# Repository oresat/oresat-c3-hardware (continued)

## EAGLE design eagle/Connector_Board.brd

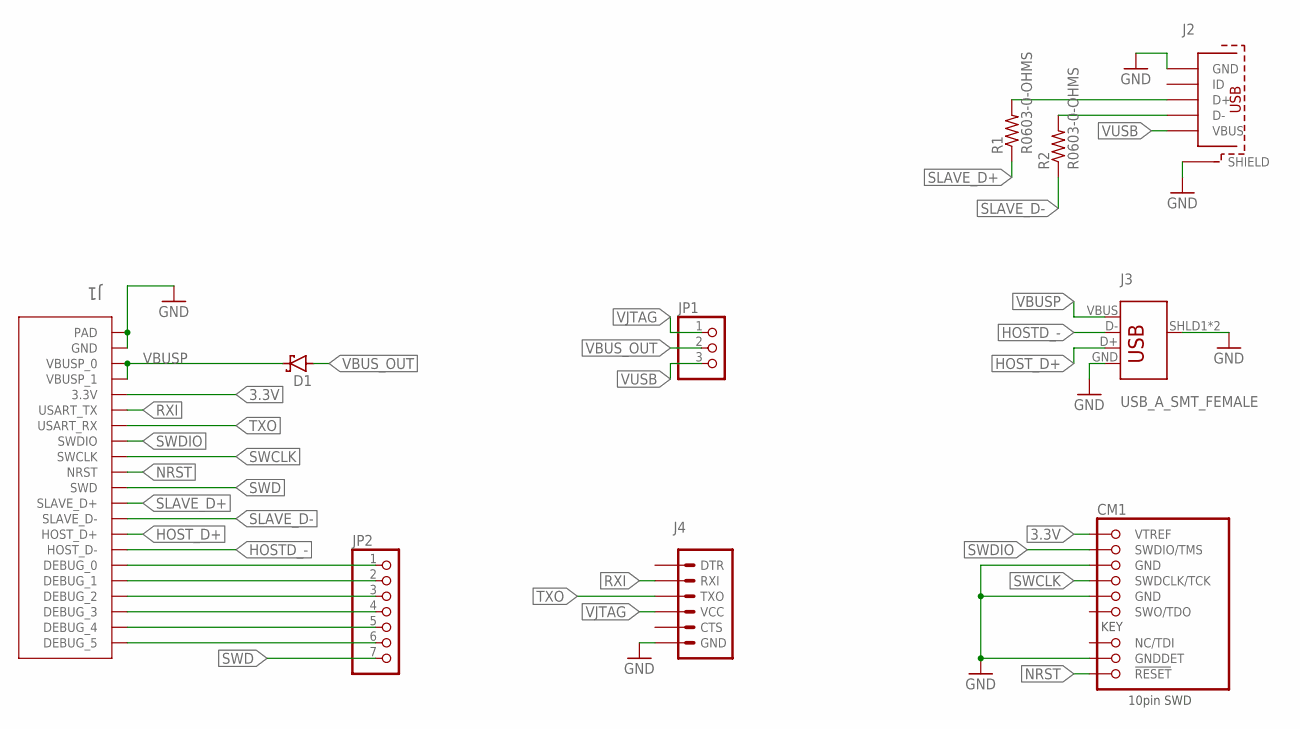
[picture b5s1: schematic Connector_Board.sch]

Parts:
CM1: FTSH-105-XX-X-DV-K; CON10_2X5_DUK_FTSH
D1: CDBU0520; DIOC1709X85N
J1: 2-1734592-0; TE_2-1734592-0
J2: MICRO-USB-SOCKET; 629105136821
J3: USB_A_SMT_FEMALE; USB-A-S-SILK-FEMALE
J4: 6_PIN_SERIAL_TARGETSILK; 6_PIN_SERIAL_TARGET_SIDE_W_SILK
JP1: PINHD-1X3; 1X03
JP2: PINHD-1X7; 1X07
R1, R2: R0603-0-OHMS; .0603-C-NOSILK

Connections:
3.3V: CM1.1 (VTREF), J1.17 (3.3V)
GND: CM1.3 (GND), CM1.5 (GND), CM1.9 (GNDDET), J1.20 (GND), J1.S1 (PAD), J1.S2 (PAD), J2.5 (GND), J2.SHELL (SHIELD), J2.SHELL1 (SHIELD), J2.SHELL2 (SHIELD), J2.SHELL3 (SHIELD), J3.GND, J3.SHLD1 (SHIELD), J3.SHLD2 (SHIELD), J4.P$6 (GND)
HOSTD_-: J1.7 (HOST_D-), J3.D-
HOST_D+: J1.8 (HOST_D+), J3.D+
unnamed: J1.6 (DEBUG_0), JP2.1
unnamed: J1.5 (DEBUG_1), JP2.2
unnamed: J1.4 (DEBUG_2), JP2.3
unnamed: J2.2 (D-), R2.2
unnamed: J2.3 (D+), R1.2
unnamed: J1.3 (DEBUG_3), JP2.4
unnamed: J1.2 (DEBUG_4), JP2.5
unnamed: J1.1 (DEBUG_5), JP2.6
NRST: CM1.10 (!RESET), J1.12 (NRST)
RXI: J1.16 (USART_TX), J4.P$3 (RXI)
SLAVE_D+: J1.10 (SLAVE_D+), R1.1
SLAVE_D-: J1.9 (SLAVE_D-), R2.1
SWCLK: CM1.4 (SWDCLK/TCK), J1.13 (SWCLK)
SWD: J1.11 (SWD), JP2.7
SWDIO: CM1.2 (SWDIO/TMS), J1.14 (SWDIO)
TXO: J1.15 (USART_RX), J4.P$2 (TXO)
VBUSP: D1.1 (C), J1.18 (VBUSP_1), J1.19 (VBUSP_0), J3.VBUS
VBUS_OUT: D1.2 (A), JP1.2
VJTAG: J4.P$4 (VCC), JP1.1
VUSB: J2.1 (VBUS), JP1.3

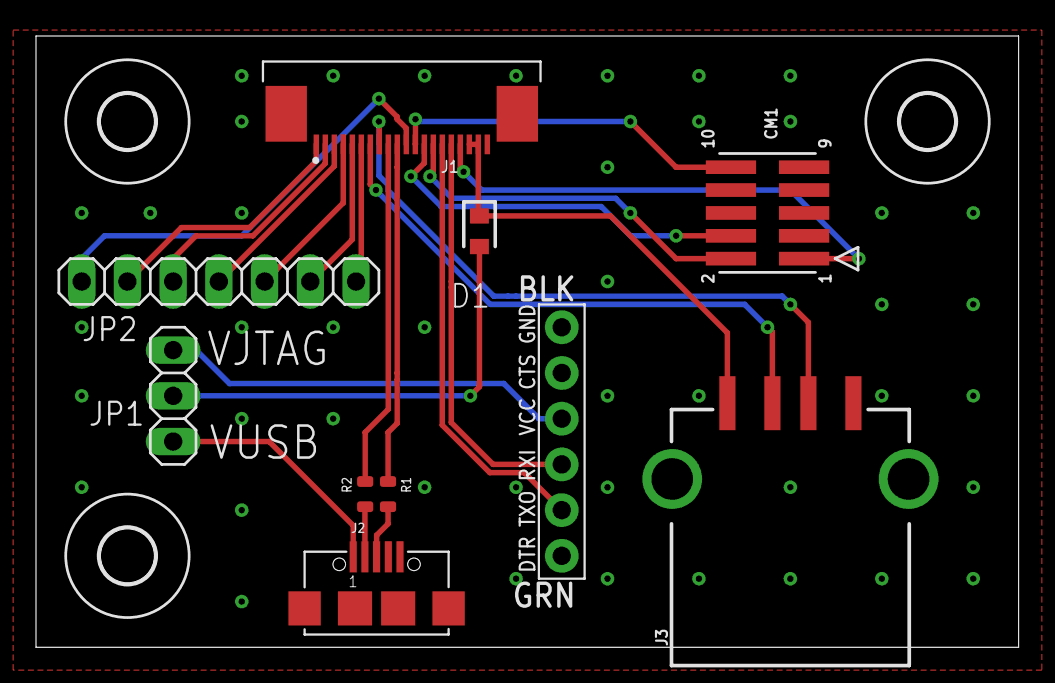
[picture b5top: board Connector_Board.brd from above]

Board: 2 copper layers, 54.6 x 34.0 mm, 13 parts (0 on the bottom side), 24 nets.

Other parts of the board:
U$1, U$2, U$3: 3,0

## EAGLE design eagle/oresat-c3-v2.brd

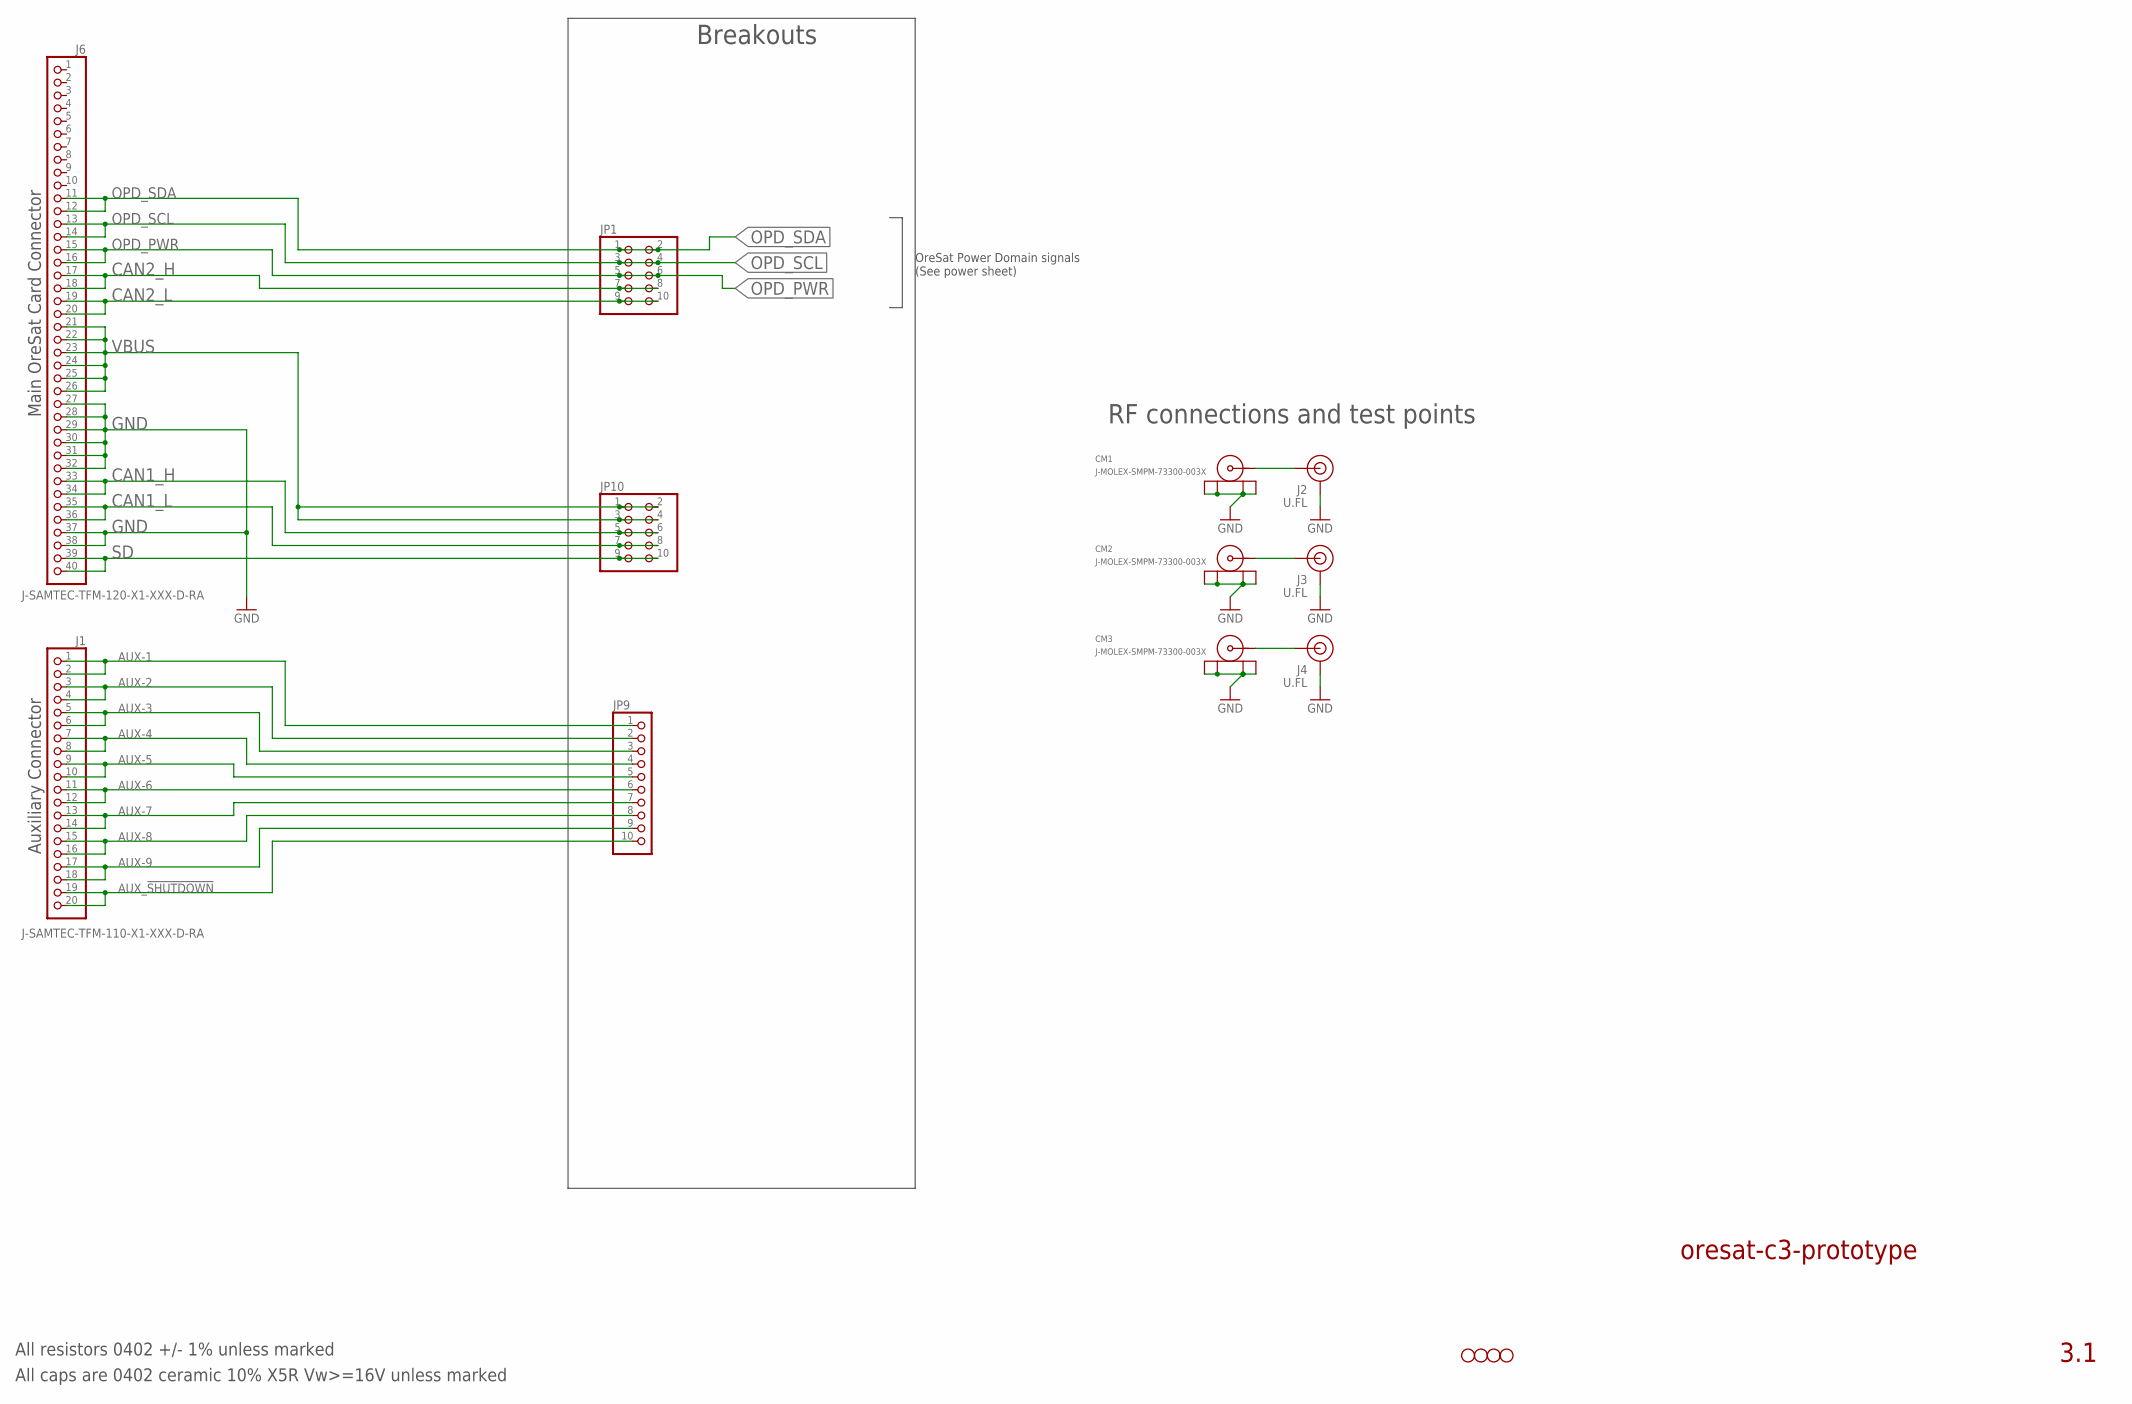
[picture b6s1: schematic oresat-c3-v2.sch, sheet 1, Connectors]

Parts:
CM1, CM2, CM3: J-MOLEX-SMPM-73300-003X; J-MOLEX-SMPM-073300-003X; MPN 73300-0020
H1, H2, H3, H4: STAND-OFFTIGHT; STAND-OFF-TIGHT
J1: J-SAMTEC-TFM-110-X1-XXX-D-RA; MPN TFM-110-01-L-D-RA
J2, J3, J4: U.FL
J6: J-SAMTEC-TFM-120-X1-XXX-D-RA; MPN TFM-120-01-L-D-RA
JP1, JP10: PINHD-2X5; 2X05
JP9: PINHD-1X10; 1X10

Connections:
AUX-1: J1.1, J1.2, JP9.1
AUX-2: J1.3, J1.4, JP9.2
AUX-3: J1.5, J1.6, JP9.3
AUX-4: J1.7, J1.8, JP9.4
AUX-5: J1.9, J1.10, JP9.5
AUX-6: J1.11, J1.12, JP9.6
AUX-7: J1.13, J1.14, JP9.7
AUX-8: J1.15, J1.16, JP9.8
AUX-9: J1.17, J1.18, JP9.9
AUX_!SHUTDOWN: J1.19, J1.20, JP9.10
CAN1_H: J6.33, J6.34, JP10.5, JP10.6; also elsewhere on the board
CAN1_L: J6.35, J6.36, JP10.7, JP10.8; also elsewhere on the board
CAN2_H: J6.17, J6.18, JP1.7, JP1.8; also elsewhere on the board
CAN2_L: J6.19, J6.20, JP1.9, JP1.10; also elsewhere on the board
GND: CM1.P$1 (SHIELD3), CM1.P$2 (SHIELD2), CM1.P$3 (SHIELD1), CM1.P$4 (SHIELD), CM2.P$1 (SHIELD3), CM2.P$2 (SHIELD2), CM2.P$3 (SHIELD1), CM2.P$4 (SHIELD), CM3.P$1 (SHIELD3), CM3.P$2 (SHIELD2), CM3.P$3 (SHIELD1), CM3.P$4 (SHIELD), J2.1 (GND), J2.2 (GND), J3.1 (GND), J3.2 (GND), J4.1 (GND), J4.2 (GND), J6.27, J6.28, J6.29, J6.30, J6.31, J6.32, J6.37, J6.38; also elsewhere on the board
unnamed: CM3.RF (CENTER), J4.FEED (SIGNAL)
OPD_PWR: J6.15, J6.16, JP1.5, JP1.6; also elsewhere on the board
OPD_SCL: J6.13, J6.14, JP1.3, JP1.4; also elsewhere on the board
OPD_SDA: J6.11, J6.12, JP1.1, JP1.2; also elsewhere on the board
RF1: CM1.RF (CENTER), J2.FEED (SIGNAL)
RF2: CM2.RF (CENTER), J3.FEED (SIGNAL)
SD: J6.39, J6.40, JP10.9, JP10.10; also elsewhere on the board
VBUS: J6.21, J6.22, J6.23, J6.24, J6.25, J6.26, JP10.1, JP10.2, JP10.3, JP10.4; also elsewhere on the board

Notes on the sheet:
oresat-c3-prototype
3.1
All resistors 0402 +/- 1% unless marked
All caps are 0402 ceramic 10% X5R Vw>=16V unless marked
Auxiliary Connector
Main OreSat Card Connector
RF connections and test points
Breakouts
OreSat Power Domain signals (See power sheet)

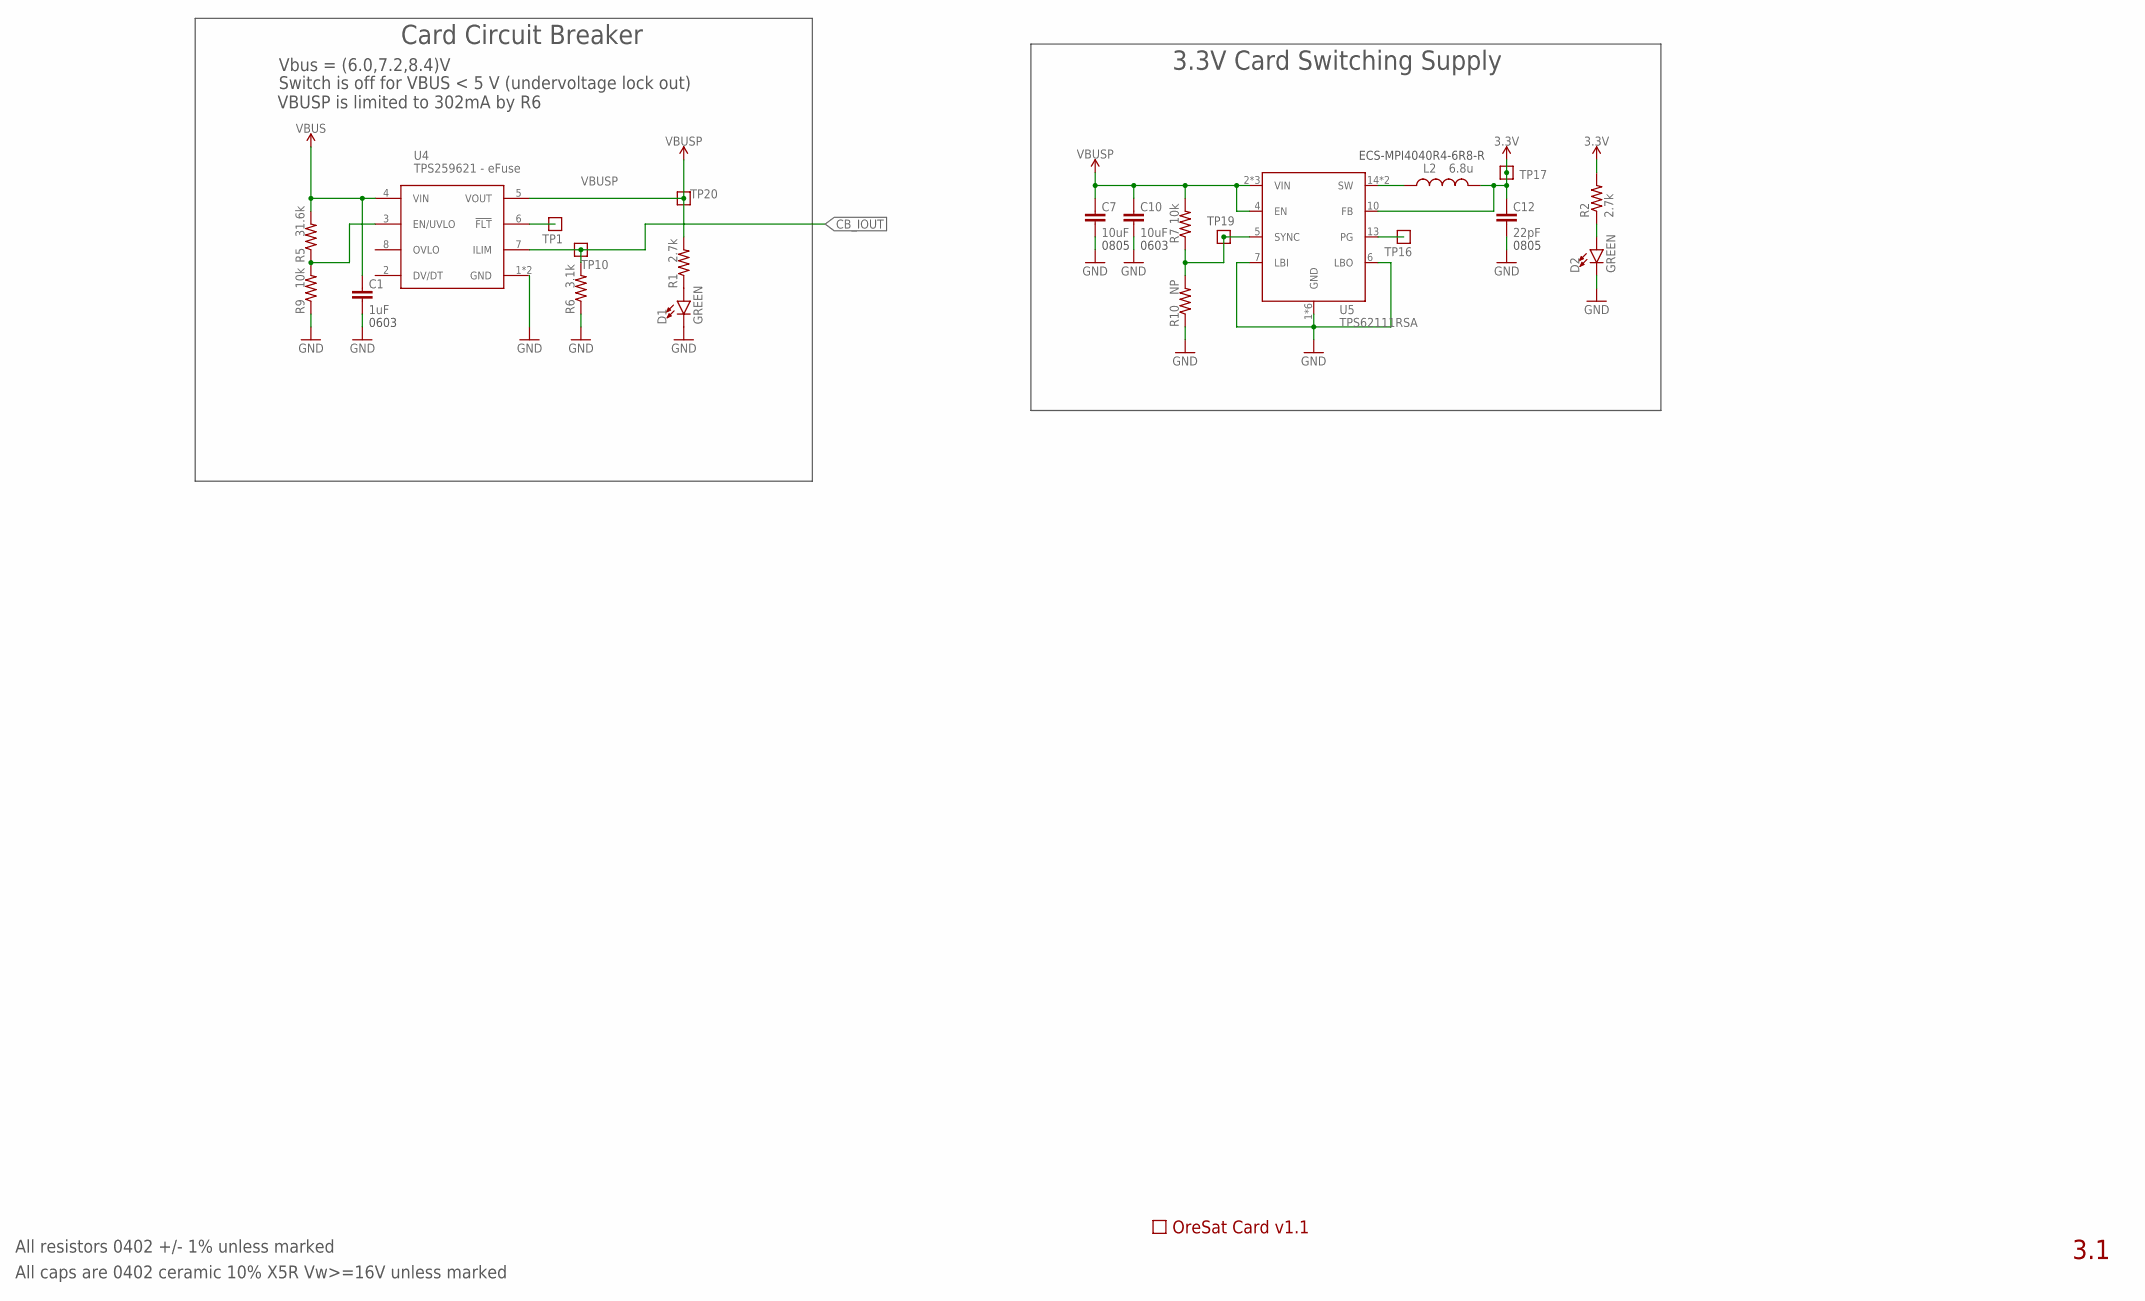
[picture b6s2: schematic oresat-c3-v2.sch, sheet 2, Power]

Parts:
C1: 1uF; .0603-B-NOSILK; MPN CL05B104KO5NNNC
C7: 10uF; .0603-B-NOSILK
C10: 10uF; .0603-B-NOSILK; MPN CL05B104KO5NNNC
C12: 22pF; .0603-B-NOSILK
D1, D2: GREEN; LED-0603
L2: 6.8u; ECS-MPI4040; MPN ECS-MPI4040R4-6R8-R
R1, R2: 2.7k; .0603-C-NOSILK; MPN RC1005F6653CS
R5: 31.6k; .0603-C-NOSILK; MPN RC1005F6653CS
R6: 3.1k; .0603-C-NOSILK; MPN RC1005F6653CS
R7, R9: 10k; .0603-C-NOSILK; MPN RC1005F6653CS
R10: NP; .0603-C-NOSILK; MPN RC1005F6653CS
TP1, TP10, TP16, TP17, TP19, TP20: TEST-POINT; 2MM-TEST-POINT
U4: TPS259621 - eFuse; SO-POWERPAD-8
U5: TPS62111RSA; S-PVQFN-16; MPN TPS62111RSA
U$1: ORESAT-CARD-V1.1-3XRF

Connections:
3.3V: C12.1, L2.2, R2.2, TP17.1, U5.10 (FB); also elsewhere on the board
!CB_FLT: TP1.1, U4.6 (!FLT)
CB_IOUT: R6.2, TP10.1, U4.7 (ILIM); also elsewhere on the board
EN/UVLO: R5.1, R9.2, U4.3 (EN/UVLO)
GND: C1.2, C7.2, C10.2, C12.2, D1.C, D2.C, R6.1, R9.1, R10.1, U4.1 (GND), U4.THERMAL (GND), U5.1 (GND), U5.6 (LBO), U5.7 (LBI), U5.9 (GND), U5.11 (GND), U5.12 (GND), U5.16 (GND), U5.PAD (GND); also elsewhere on the board
unnamed: D1.A, R1.1
unnamed: D2.A, R2.1
TPS62111-PG: TP16.1, U5.13 (PG)
TPS62111-SYNC: R7.1, R10.2, TP19.1, U5.5 (SYNC)
TPS62111_SW: L2.1, U5.14 (SW), U5.15 (SW)
VBUS: C1.1, R5.2, U4.4 (VIN); also elsewhere on the board
VBUSP: C7.1, C10.1, R1.2, R7.2, TP20.1, U4.5 (VOUT), U5.2 (VIN), U5.3 (VIN), U5.4 (EN), U5.8 (VIN); also elsewhere on the board

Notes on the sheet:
0805
0603
ECS-MPI4040R4-6R8-R
3.3V Card Switching Supply
3.1
Vbus = (6.0,7.2,8.4)V
Card Circuit Breaker
Switch is off for VBUS < 5 V (undervoltage lock out)
VBUSP is limited to 302mA by R6
All resistors 0402 +/- 1% unless marked
All caps are 0402 ceramic 10% X5R Vw>=16V unless marked

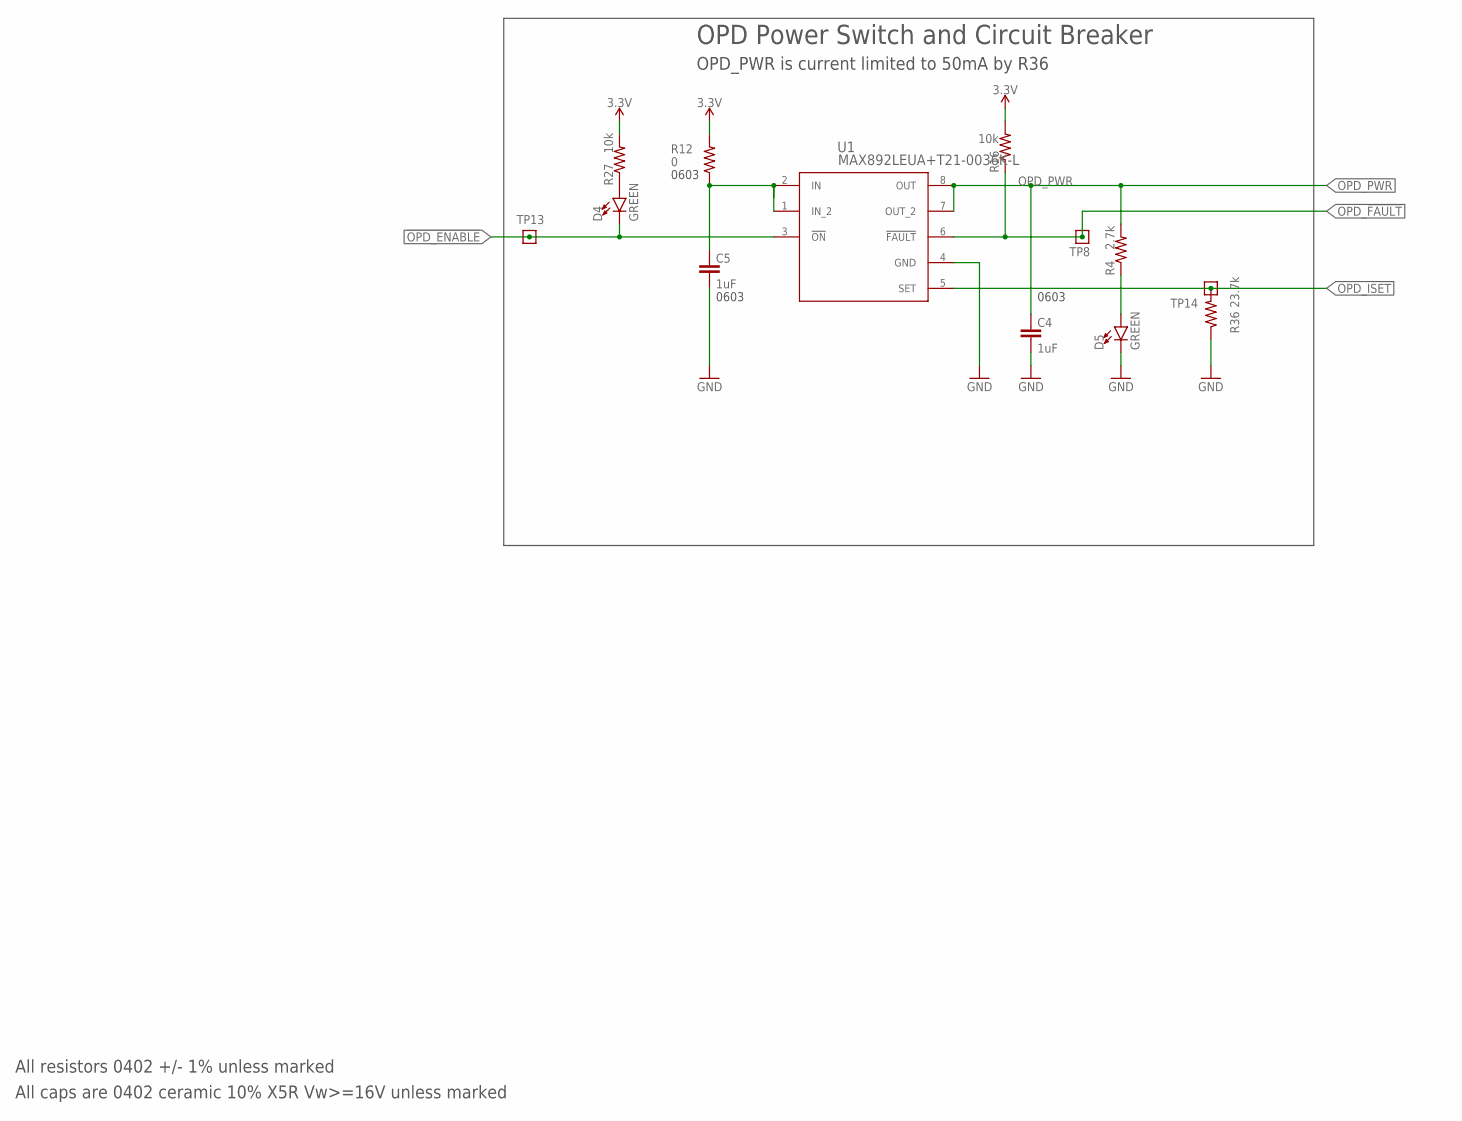
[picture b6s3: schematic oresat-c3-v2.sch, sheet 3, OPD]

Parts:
C4, C5: 1uF; .0603-B-NOSILK; MPN CL05B104KO5NNNC
D4, D5: GREEN; LED-0603
R4: 2.7k; .0603-C-NOSILK; MPN RC1005F6653CS
R12: 0; .0603-C-NOSILK; MPN RC1005F6653CS
R16, R27: 10k; .0603-C-NOSILK; MPN RC1005F6653CS
R36: 23.7k; .0603-C-NOSILK; MPN RC1005F6653CS
TP8, TP13, TP14: TEST-POINT; 2MM-TEST-POINT
U1: MAX892LEUA+T21-0036K-L; 21-0036K-L

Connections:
3.3V: R12.2, R16.2, R27.2; also elsewhere on the board
!OPD_ENABLE: D4.C, TP13.1, U1.3 (!ON); also elsewhere on the board
GND: C4.2, C5.2, D5.C, R36.1, U1.4 (GND); also elsewhere on the board
unnamed: D4.A, R27.1
unnamed: D5.A, R4.1
OPD-3.3V: C5.1, R12.1, U1.1 (IN_2), U1.2 (IN)
OPD_!FAULT: R16.1, TP8.1, U1.6 (!FAULT); also elsewhere on the board
OPD_ISET: R36.2, TP14.1, U1.5 (SET); also elsewhere on the board
OPD_PWR: C4.1, R4.2, U1.7 (OUT_2), U1.8 (OUT); also elsewhere on the board

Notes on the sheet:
0603
OPD Power Switch and Circuit Breaker
OPD_PWR is current limited to 50mA by R36
All resistors 0402 +/- 1% unless marked
All caps are 0402 ceramic 10% X5R Vw>=16V unless marked

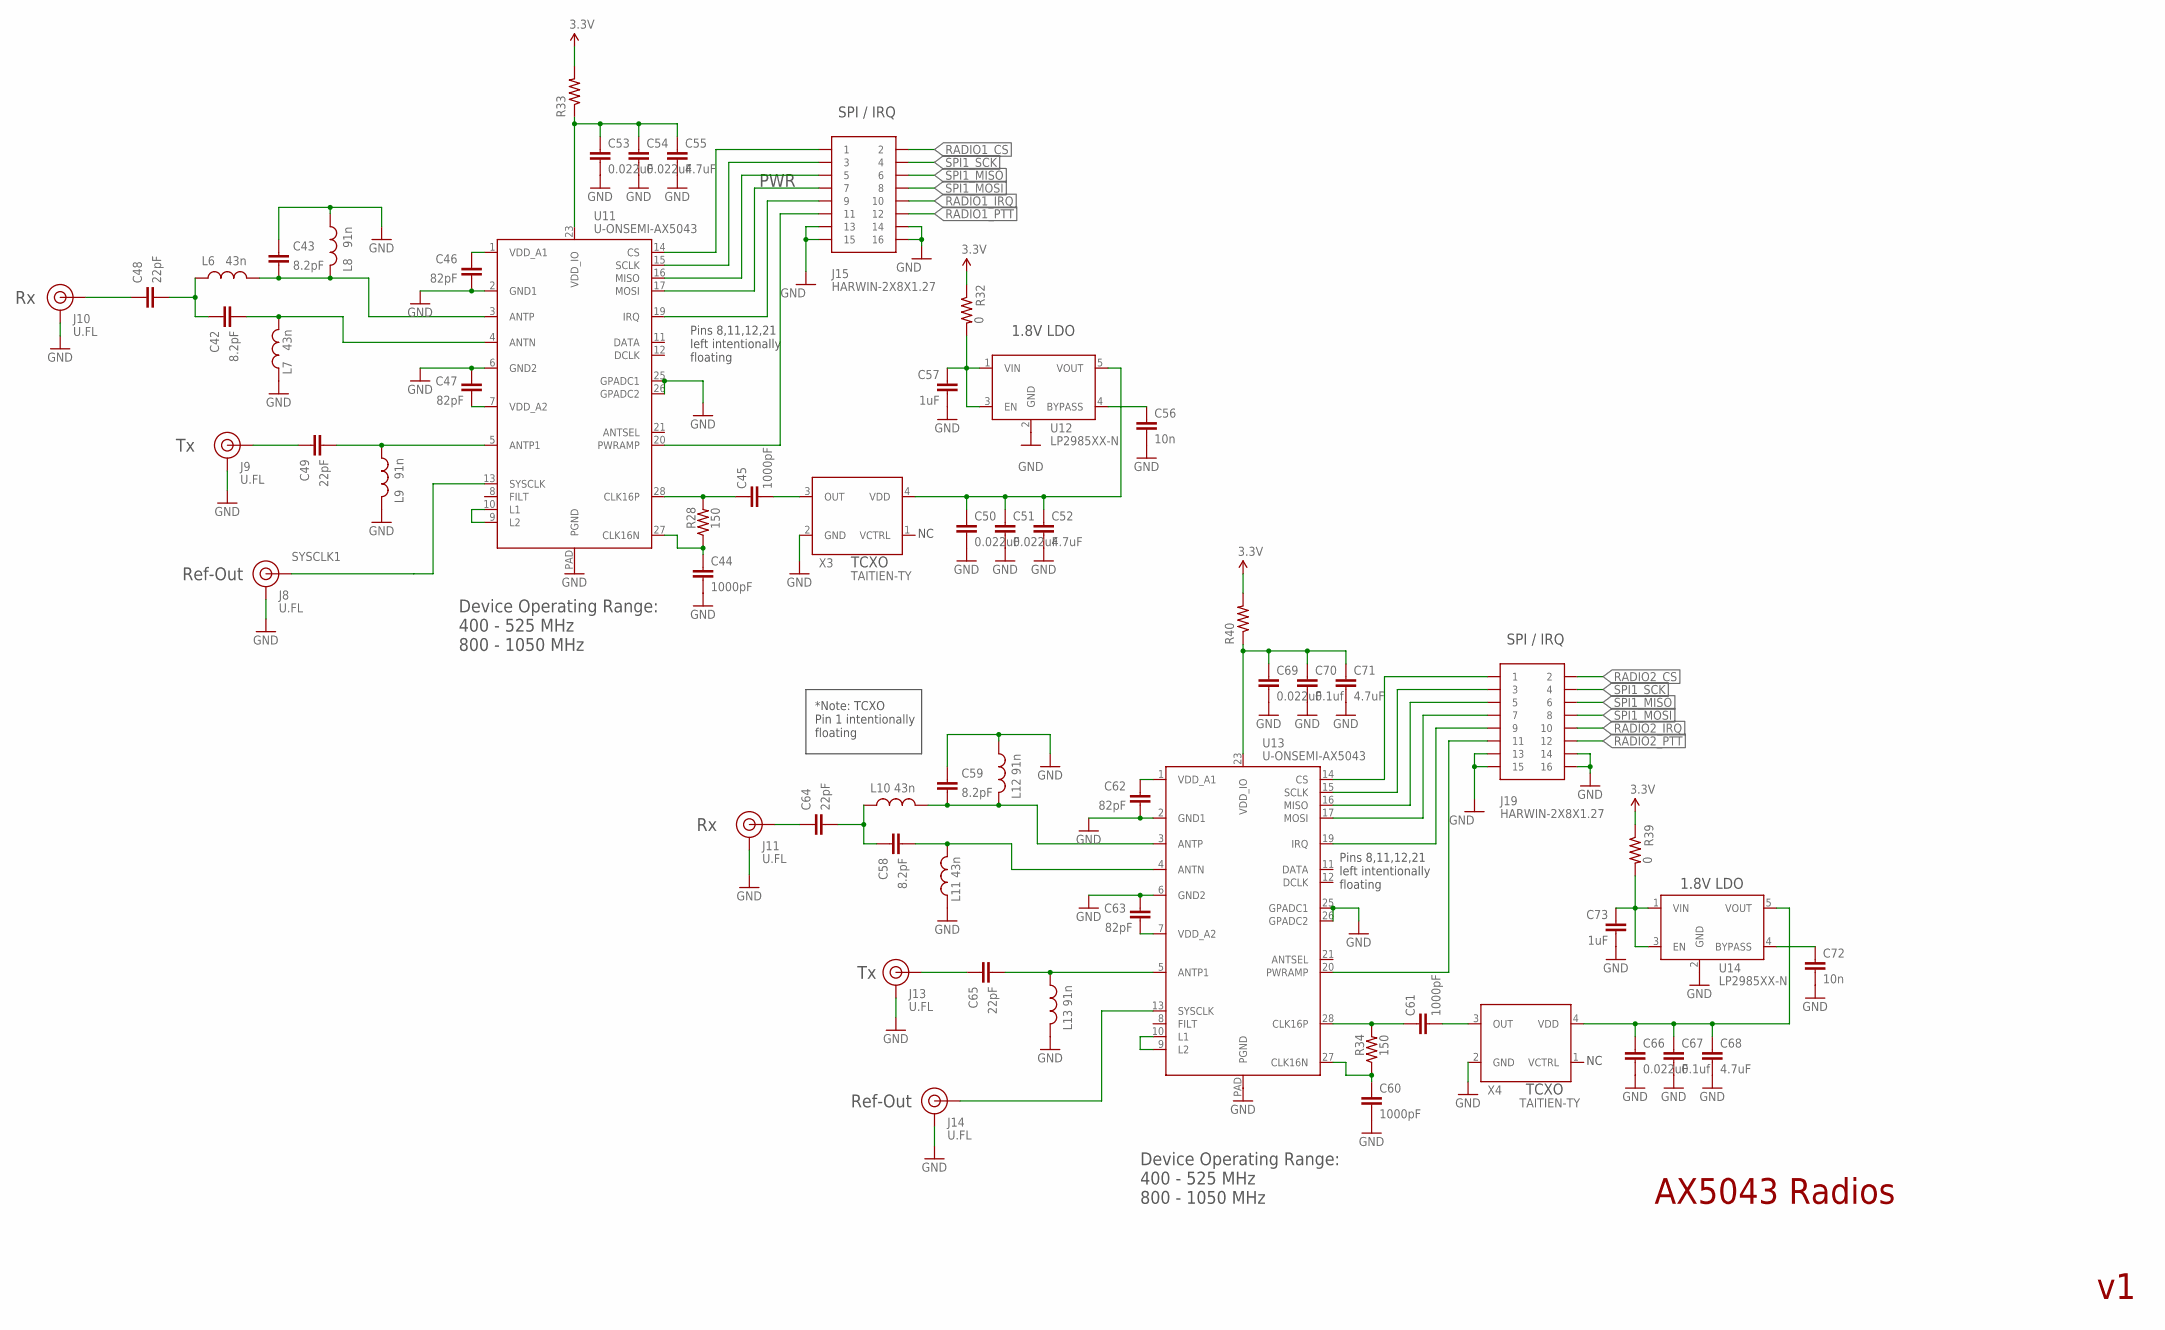
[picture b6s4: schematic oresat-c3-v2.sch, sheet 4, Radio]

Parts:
C42, C43, C58, C59: 8.2pF; .0603-B-NOSILK
C44, C45, C60, C61: 1000pF; .0603-B-NOSILK
C46, C47, C62, C63: 82pF; .0603-B-NOSILK
C48, C49, C64, C65: 22pF; .0603-B-NOSILK
C50, C51, C53, C54, C66, C69: 0.022uF; .0603-B-NOSILK
C52, C55, C68, C71: 4.7uF; .0603-B-NOSILK
C56, C72: 10n; .0603-B-NOSILK
C57, C73: 1uF; .0603-B-NOSILK
C67, C70: 0.1uf; .0603-B-NOSILK
J8, J9, J10, J11, J13, J14: U.FL
J15, J19: HARWIN-2X8X1.27; 2X8X1.27
L6, L7, L10, L11: 43n; .0402-C-NOSILK
L8, L9, L12, L13: 91n; .0603-C-NOSILK
R28, R34: 150; .0603-C-NOSILK
R32, R33, R39, R40: 0; .0603-C-NOSILK
U11, U13: U-ONSEMI-AX5043; QFN28-5X5-WITH-CENTER-PAD
U12, U14: LP2985XX-N; SOT-23
X3, X4: TAITIEN-TY; 2.5X2.0

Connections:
1V1: C50.1, C51.1, C52.1, U12.5 (VOUT), X3.4 (VDD)
1V2: C66.1, C67.1, C68.1, U14.5 (VOUT), X4.4 (VDD)
3.3V: R32.1, R33.2, R39.1, R40.2; also elsewhere on the board
ANTN1: C42.2, L7.2, U11.4 (ANTN)
ANTN2: C58.2, L11.2, U13.4 (ANTN)
ANTP2: C43.2, L6.2, L8.1, U11.3 (ANTP)
ANTP3: C49.2, L9.2, U11.5 (ANTP1)
ANTP4: C59.2, L10.2, L12.1, U13.3 (ANTP)
ANTP5: C65.2, L13.2, U13.5 (ANTP1)
CLKN1: C44.1, R28.1, U11.27 (CLK16N)
CLKN2: C60.1, R34.1, U13.27 (CLK16N)
CLKP1: C45.1, R28.2, U11.28 (CLK16P)
CLKP2: C61.1, R34.2, U13.28 (CLK16P)
CS1: J15.1, U11.14 (CS)
CS2: J19.1, U13.14 (CS)
GND: C43.1, C44.2, C46.2, C47.1, C50.2, C51.2, C52.2, C53.2, C54.2, C55.2, C56.2, C57.2, C59.1, C60.2, C62.2, C63.1, C66.2, C67.2, C68.2, C69.2, C70.2, C71.2, C72.2, C73.2, J8.1 (GND), J8.2 (GND), J9.1 (GND), J9.2 (GND), J10.1 (GND), J10.2 (GND), J11.1 (GND), J11.2 (GND), J13.1 (GND), J13.2 (GND), J14.1 (GND), J14.2 (GND), J15.13, J15.14, J15.15, J15.16, J19.13, J19.14, J19.15, J19.16, L7.1, L8.2, L9.1, L11.1, L12.2, L13.1, U11.2 (GND1), U11.6 (GND2), U11.25 (GPADC1), U11.26 (GPADC2), U11.PAD (PGND), U12.2 (GND), U13.2 (GND1), U13.6 (GND2), U13.25 (GPADC1), U13.26 (GPADC2), U13.PAD (PGND), U14.2 (GND), X3.2 (GND), X4.2 (GND); also elsewhere on the board
IRQ1: J15.9, U11.19 (IRQ)
IRQ2: J19.9, U13.19 (IRQ)
MISO1: J15.5, U11.16 (MISO)
MISO2: J19.5, U13.16 (MISO)
MOSI1: J15.7, U11.17 (MOSI)
MOSI2: J19.7, U13.17 (MOSI)
unnamed: C64.1, J11.FEED (SIGNAL)
unnamed: U11.9 (L2), U11.10 (L1)
unnamed: C46.1, U11.1 (VDD_A1)
unnamed: C47.2, U11.7 (VDD_A2)
unnamed: C56.1, U12.4 (BYPASS)
unnamed: C42.1, C48.2, L6.1
unnamed: C45.2, X3.3 (OUT)
unnamed: U13.9 (L2), U13.10 (L1)
unnamed: C62.1, U13.1 (VDD_A1)
unnamed: C63.2, U13.7 (VDD_A2)
unnamed: C72.1, U14.4 (BYPASS)
unnamed: C58.1, C64.2, L10.1
unnamed: C61.2, X4.3 (OUT)
PWRAMP1: J15.11, U11.20 (PWRAMP)
PWRAMP2: J19.11, U13.20 (PWRAMP)
RADIO1_CS: J15.2; also elsewhere on the board
RADIO1_IRQ: J15.10; also elsewhere on the board
RADIO1_PTT: J15.12
RADIO2_CS: J19.2; also elsewhere on the board
RADIO2_IRQ: J19.10; also elsewhere on the board
RADIO2_PTT: J19.12
RX1: C48.1, J10.FEED (SIGNAL)
SCLK1: J15.3, U11.15 (SCLK)
SCLK2: J19.3, U13.15 (SCLK)
SPI1_MISO: J15.6, J19.6; also elsewhere on the board
SPI1_MOSI: J15.8, J19.8; also elsewhere on the board
SPI1_SCK: J15.4, J19.4; also elsewhere on the board
SYSCLK1: J8.FEED (SIGNAL), U11.13 (SYSCLK)
SYSCLK2: J14.FEED (SIGNAL), U13.13 (SYSCLK)
TX1: C49.1, J9.FEED (SIGNAL)
TX2: C65.1, J13.FEED (SIGNAL)
VDD_IO-1: C53.1, C54.1, C55.1, R33.1, U11.23 (VDD_IO)
VDD_IO-2: C69.1, C70.1, C71.1, R40.1, U13.23 (VDD_IO)
VIN-1V8-1: C57.1, R32.2, U12.1 (VIN), U12.3 (EN)
VIN-1V8-2: C73.1, R39.2, U14.1 (VIN), U14.3 (EN)

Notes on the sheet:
AX5043 Radios
Ref-Out
PWR
Device Operating Range: 400 - 525 MHz 800 - 1050 MHz
SPI / IRQ
1.8V LDO
TCXO
Pins 8,11,12,21 left intentionally floating
*Note: TCXO Pin 1 intentionally floating

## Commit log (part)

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2019-10-17 Started some simple documentation
2019-10-18 Added device proposal as per Practicum requirements
2019-10-30 Initial commit of V3 protocard based C3 prototype
2019-10-31 adding videos
2019-11-02 MPP File
    Updated 2 tasks to add.
2019-11-06 Most F4 nets labelled. Connected to OPD CB.
2019-11-07 connected CAN bus chips
2019-11-07 Update Gantt .mpp file and pdf
    Added names to tasks on .mpp file. Removed Gantt_2.pdf, replaced with updated Gantt_1.pdf. Never needed a Gantt_2 to begin with.
2019-11-07 Cleaning up board layout
2019-11-07 Added OPD and CAN2 connector
2019-11-14 layed out most of the board awaiting review and adding BOM
2019-11-14 Routed spare pins to header and a little cleanup
2019-11-15 Fixed VBUSP routing around the SPS
2019-11-17 Added the Radio breakout board schematic and layout to the eagle folder under DVK2C-breakout.sch
2019-11-18 adding it back
2019-11-19 Added radio pins, added supply pin capacitors, moved some components
2019-11-20 made some connections
2019-11-21 added MCU test points
2019-11-21 cleaned up a little bit, connected last few routes
2019-11-21 Fixed some DRC errors
2019-11-21 passed DRC
2019-11-21 Added TP for one last MCU pin
2019-11-24 Fix VCAP, fix JTAG header, remove weird 0.1in headers which make SPI bus go everywhere, fix component tyes, add test points, polish.
2019-11-25 Replaced new ICs with versions in the oresat-eagle-libraries repo
2019-11-26 Added the BOM for the practicum C3 board
2019-12-07 added the XTAL data sheet
2019-12-12 Adding some documentation links
2020-01-19 Note for replacing SD card with eMMC
    hand written eMMC notes
2020-01-20 Added eMMC
    Almost completed adding eMMC
2020-01-21 Make changes to oresat-c3-v1 board
    Fix eMMC pin out to better match datasheet
    Route data lines to match lengths
2020-01-22 implemented changes after design Review with Andrew
2020-01-22 Updated eMMC Notes
2020-01-23 Housekeeping
    Put homeworks from Fall 2019 Practicum into their own folder.
2020-01-24 Made Design review changes to C3 board
    updated changes made in design review doc
2020-01-24 Replace lost wire
2020-01-25 Fix some connections
2020-01-25 Changed pads and via layout under RF
2020-01-31 A wee bit of polish to get it off to OSH Park. v1 sent to fab.
2020-01-31 version 2 created
2020-02-06 Parts Move so far
    not completed
2020-02-14 Create vSupUT01VS33D - Cobham Voltage Supervisor.pdf
    Added voltage supervisor datasheet.
2020-02-17 Work in progress
    Moving and making room for radio
2020-02-18 Updated Layout Notes
    updated eMMC notes and added move notes for making room for split plane
2020-02-20 Removed jumper Fixed DRC errors
2020-02-21 Minor adjustments
    Minor adjustments to edge connector and labeling, shifted some of the Watchdog circuit
2020-02-23 Added TVS Diode Datasheet
    OPD Protection Circuit TVS Diode Datasheet.
2020-02-29 put in segregated ground planes, added the version of the project proposal that was signed to the docs folder
2020-03-03 Added TVS diodes for watchdog and OPD
2020-03-06 Added a design blocks folder for RF integration
2020-03-06 Added UDH power tree dbl
2020-03-07 Allocated MCU pins for deployment system, sythnesizer control, and feedback. Added initial deployment circuitry.
2020-03-07 Changes made to the watchdog
2020-03-08 Connected UHF/ UHF Power Tree (mostly)
2020-03-09 Edit WDT Symbol and Removed TVS on SD line
    Moved WDI onto left side of WDT symbol. Removed U8 (TVS Diodes connected to SD line)
2020-03-15 Making room for when we change MCU
2020-03-16 completed making room for new MCU
    Made many design review changes
    removed all temp save files
2020-03-17 swapped the L-band and UHF areas
2020-03-20 Replaced parts form tova library with their own library components
2020-03-22 Made changes after Vigely's L Band review
2020-03-22 Fixed U17
2020-03-23 Added Supplys after Zero ohm resistors for 3.3V sources
2020-03-24 Design review changes
    L-band 2.5V LDO bypass 10n
    Use same LDO for UHF 3.3V Lp2985
    Put 1% on resistor note.
    Put working voltage on caps note.
    Run A MASSIVE trave From the 5V SPS to the UHF
    Break up the pad on tcream layer under the power pads for the solder stencils
2020-03-25 DRC clean up , Fixed small Test Points
2020-03-25 Added 100k pull up resistors on the LDO's
2020-03-26 more desing review changes
2020-03-26 Removed more Airwires
2020-03-27 Rerouted the VBUS from edge connector
2020-03-27 added some test points and 0 ohms to UHF RF path
2020-03-30 Finished adding test pads and 0hms to the L band RF path
2020-04-02 Added WDT band-aide
2020-04-10 updated some testpoints
2020-04-10 Fixed Airwires; wire stubs Approved warnings
2020-04-14 retired some 04/12 design review items
2020-04-14 Final design rule changes Made
2020-04-16 v2 OFF TO FABgit status Lots of cleanup on TNAMEs, cleanup on solder mask openings for microstrips, a bit of power rework near AX5043s. TODO: Make all 0603 components the smaller C version, which can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
2020-04-28 Edited Attributes
2020-04-28 Finished adding UHF part attributes for BOM generation
2020-04-29 Fix Sync Error
2020-05-14 Move some BOM files
2020-05-17 Connecting in new 100 pin Microprocessor
2020-05-17 Made Sure Resistor values are shown on schematic
2020-06-11 Re push Changes made to watchdog and Antenna deplayment
2020-06-11 Changed capacitors for the watchdog
2020-06-26 Minor cleanup and clearing ERC and DRC
2020-06-26 Clean up Libraries, Worked on BOM for V3
2020-06-29 Change text dimensions
2020-07-20 Tried to fix EAGLE errors for OSH Park; failed, we need to make Gerbers for them.
2020-07-28 Added part attributes for the dual pch mosfets
2020-08-18 Added PA design block , Replaced u Processor, Fixed/replaced X1 crystal
2020-08-23 Added updated UHF PA design block
2020-08-23 Moved UHF PA to UHF Sheet
2020-08-26 Added tstop and Power to UHF PA
2020-08-28 design information added for PA UHF
2020-09-18 Added TOT schematic for UHF
2020-10-13 minor clean up of schematic and added split planes back in for radios
2020-12-14 UHF section: rough draft done. Moved 5V SPS closer to PA, shifted over 0.1 connector, revamped the time-out-timer (TOT) to be way smaller and use the right logic in smaller packages. Moved the whole 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
2020-12-31 Giant massage of parts to get more room for RTCs, and put some room between modular blocks.
2021-01-02 UHF section review and polish done. L Band 50% done. Then TNAME, and .. done?
2021-01-03 Added FRAM, because FRAMgit add oresat-c3.brd oresat-c3.sch, added 5th order LPF for UHF TX. Waiting on final values of LPF and time out timer (TOT) from Glenn, then need to fix attributes and ship!
2021-01-04 Fixed up PA TSTOP and TCREAM, fixed quad nchannel TCREAM, added call signs of main C3 folks, fixed 2mm miter on RF lines.
2021-02-07 Changes to the timeout timer based on available parts; updated SCH and BOM. Also fixed off-by-one-row errors for Mouser parts.
2021-02-07 Updated to the CERN-OHL-S v2!
2021-02-14 Fixed swap of pins 2 and 3 on the TOT; renamed TOT pins to be better names (TOT_OUT is now !TOT_PA_DISABLE).
2021-02-16 Fixed some DRC issues.
2021-03-08 Updated TOT values to make it 1 second long. Added "RF test points" and some associated ground points with level values to help future debugging.
    UGH: in previous commit, forgot to mention the most important fixes:
    - Fixed TOT swap of pin 2,3 and the non-working functionality of the !SHDN. M4 now unlatches output only, and does not affect output of the circuit.
    - Fixed WDT with latest "Tim" version (thanks Tim!) with small changes to values to operate correctly.
2021-03-08 Minor polishing with Glenn, removed L band TX components, fixed BOM.
2022-10-09 Added KiCad C3 import
2022-12-29 Switched to v2 backplane connector, removed GPS RF.
2022-12-30 Fixes #39 - added ILIM to ADC on PA3 via 10K resistor.
2022-12-30 Fixes #40 - more capacitance on 3.3V SPS in and out to help with brownouts.
2023-03-16 Converted kicad directory over to our latest Octavo-based v6 design starting from the GPS card.
2023-04-16 Started moving RF schematic bits over to KiCad
2023-05-03 Rough draft of watchdog and I2C system schematics.
2023-05-05 Simulated 30 second v6 watchdog circuit and fixed up watchdog in KiCAD.
2023-05-31 Big cleanup on UHF radio; about 50% done.
2023-06-01 Flipped UHF schematic to be L to R, more polish, added direction arrows. Started on L band radio. Added latest oresat-kicad libraries, started to remove old libraries (e.g., GPS).
2023-06-02 Sane amount of ERC errors now; mostly library cleanups.
2023-06-03 Updated all footprints for sheet one of the schematic.
2023-06-04 working on power sheet.
2023-06-08 Updated test points, fixed some more hidden ERCs.
2023-06-22 Fixed footprints and laid out WDT and OPD circuitry.
2023-06-23 Moved octavo and emmc over radio. It's going to be tight, but it looks doable. started L band layout.
2023-06-26 More radio cleanup!
2023-06-29 Rough draft of L band radio complete; committing in order to start really screwing around with ground planes.
2023-06-29 Zero airwires! Rough draft schematic and layout are done. Still need ERC and DRC and full design review and stiching and polish.
2023-07-05 More DRC cleanup. Now below 400.
2023-08-24 More polish; fixed all non-RF DRCs.
2023-08-27 Ryan made me do it: added CAN0 tranceiver.
2023-08-28 First round of BOM fixes and optimizations.
2023-08-29 ignore build directories
2023-09-04 Fixed part name, removed solder mask from the back of some of the library components for venting.
2023-11-01 Add expected dBm values on radio TX and RXs.
2023-11-19 Real part numbers for FB parts, routed signals for the UHF_ENABLE AND L_BAND_ENABLE signals.
2024-01-05 Minor DRC changes
2024-03-18 Fixed Q1 in the I2C subsystem, which was backward but we never noticed. Removed hardware ID resistors and added back in test points, since HW ID is now stored in internal EEPROM. Updated power measur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
2024-04-01 OOof, almost ordered with incorrect RF netclass. Reset to 0.5 mm keepouts.
2024-04-09 Updated readme!
2025-11-11 added and rerouted new debug connector, added a few test points
2025-12-28 Removed old EAGLE files, renamed kicad directory to the card directory.
2026-02-02 Replaced AX5043 for UHF and added TX/RX switch control
2026-02-02 started routing UHF and L band chip replacement on PCB
2026-02-18 schematic changes following design review
2026-02-21 More progress on schematic from design review, routed new debug connector and updated balun routing
2026-03-04 Design review on power and RF
2026-03-08 added mask on RF traces and fixed UHF power routing
2026-03-15 Routing complete; on to cleanup!
2026-03-16 UHF optimized. Ready for polishing
2026-03-17 All footprints updated. Passes ERC/DRC.
2026-03-18 Clean up local directory - remove old cruft from schematic and old EAGLE import libraries
2026-03-18 Fix a bunch of 3D models
2026-03-19 Upgrade makefile to create README.pdf using pandoc and sed. Polish up README.md to be more consistant and emphasize IPC-2581.
2026-03-19 Fixed some RF DRC errors, and then added two custom rules to get rid of the pesky RF errors which leaves us with ZERO DRC errorsgit add .!
2026-03-22 Changed WDT tantalums to space-rated tantalums (fun) and fixed some BOM issues. Also possibly more silk screen cleanup.
2026-04-01 BOM only change: Upgraded single gate inverter to AEC qualified version
2026-04-21 Update .gitignore to kicad 10
